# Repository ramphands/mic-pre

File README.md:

# mic-pre
battery-powered ultra-small electret microphone preamp for synth/Monome Norns/field recording
yup

two versions:

 * Battery-mounted w/power switch and jacks
    - 
    - Mouser cart: https://www.mouser.com/ProjectManager/ProjectDetail.aspx?AccessID=81b8966b79

* Microphone-mounted *aka* "Tiny Mic Pre" (to fit Ø6mm inside diameter steel/alu/brass tubing)
    - 
    - Mouser cart: https://www.mouser.com/ProjectManager/ProjectDetail.aspx?AccessID=1ea3a70ac9  
    (NOTE - for this version you **MUST** use the specified tantalum capacitors if you plan to fit the completed module into a Ø6mm ID housing.  Most tantalums will be too tall, preventing the module from fitting the tubing)

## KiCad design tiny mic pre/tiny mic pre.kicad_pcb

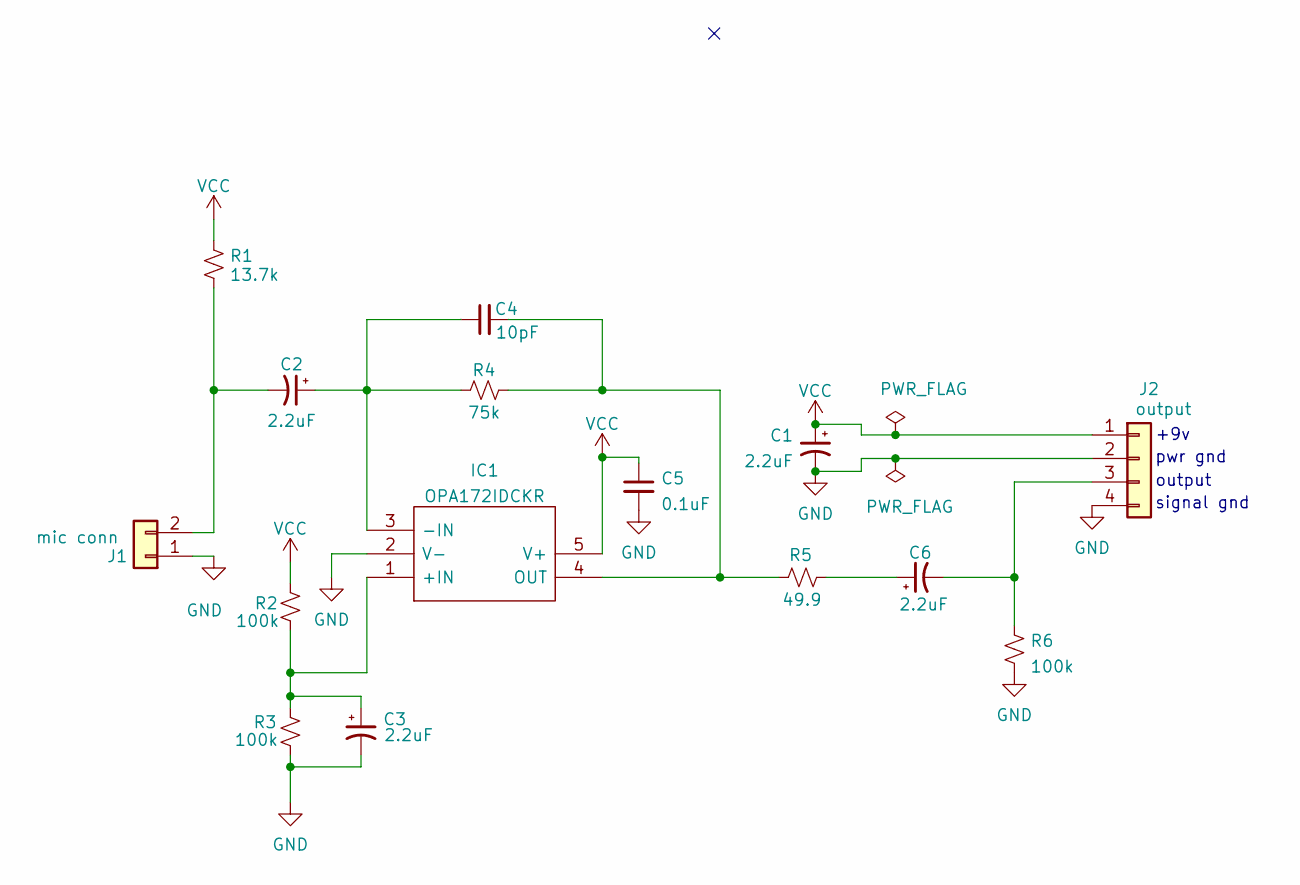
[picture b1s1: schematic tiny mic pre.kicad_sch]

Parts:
C1, C2, C3, C6: 2.2uF; CP_EIA-2012-15_AVX-P_Pad1.30x1.05mm_HandSolder
C4: 10pF; C_0603_1608Metric_Pad1.08x0.95mm_HandSolder
C5: 0.1uF; C_0603_1608Metric_Pad1.08x0.95mm_HandSolder
IC1: OPA172IDCKR; SOT-353_SC-70-5_Handsoldering; Mouser Part Number 595-OPA172IDCKR
J1: mic conn; POM-353P-3-R electret
J2: output; Pins_1x04_2.54mm_TH_SWD; Part Number 1-0401FBV0T
R1: 13.7k; R_0603_1608Metric_Pad0.98x0.95mm_HandSolder
R2, R3, R6: 100k; R_0603_1608Metric_Pad0.98x0.95mm_HandSolder
R4: 75k; R_0603_1608Metric_Pad0.98x0.95mm_HandSolder
R5: 49.9; R_0603_1608Metric_Pad0.98x0.95mm_HandSolder

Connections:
GND: C1.2, C3.2, C5.2, IC1.2 (V-), J1.1, J2.2, J2.4, R3.2, R6.2
unnamed: C2.1, C4.1, IC1.3 (-IN), R4.1
unnamed: C2.2, J1.2, R1.2
unnamed: C3.1, IC1.1 (+IN), R2.2, R3.1
unnamed: C4.2, IC1.4 (OUT), R4.2, R5.1
unnamed: C6.1, R5.2
unnamed: C6.2, J2.3, R6.1
VCC: C1.1, C5.1, IC1.5 (V+), J2.1, R1.1, R2.1

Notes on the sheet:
+9v
pwr gnd
output
signal gnd

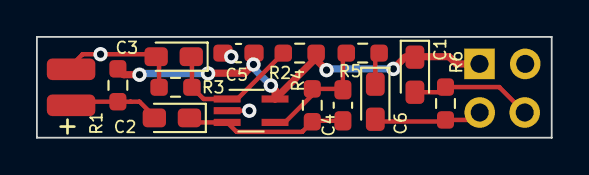
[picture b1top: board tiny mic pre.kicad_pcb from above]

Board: 2 copper layers, 28.6 x 5.6 mm, 15 parts (0 on the bottom side), 8 nets.

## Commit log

2022-03-27 Create mic-pre
